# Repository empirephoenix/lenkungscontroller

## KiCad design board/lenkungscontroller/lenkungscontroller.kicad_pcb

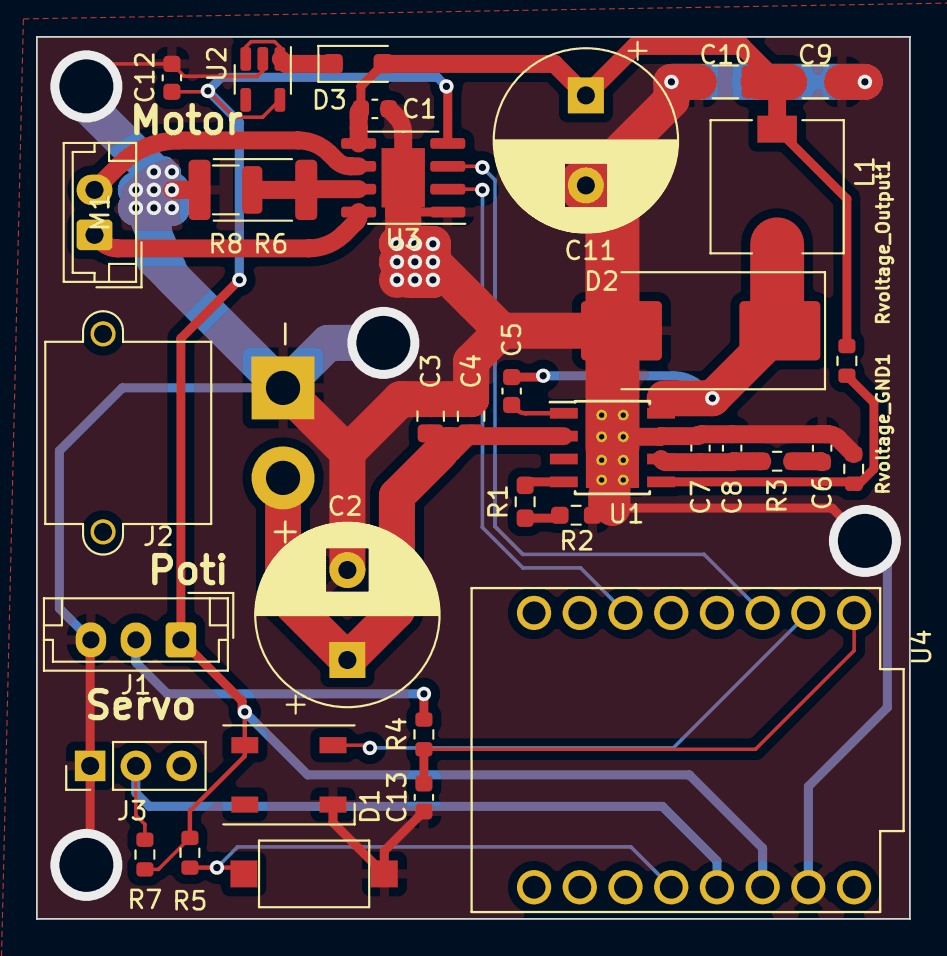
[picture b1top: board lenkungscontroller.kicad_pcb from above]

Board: 2 copper layers, 48.5 x 49.0 mm, 36 parts (0 on the bottom side), 22 nets.

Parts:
Boot1: Boot; SW_SPST_CK_RS282G05A3
C1: 220nF 50v x5r; C_0603_1608Metric
C2: 220uF; CP_Radial_D10.0mm_P5.00mm
C3, C4: 2.2uF 60V; C_0805_2012Metric
C5, C13: 100nF; C_0603_1608Metric
C6: 6800pF; C_0603_1608Metric
C7, C8: 39pf; C_0603_1608Metric
C9, C10: 47uF; C_1206_3216Metric
C11: 1000uF; CP_Radial_D10.0mm_P5.00mm
C12: 22uF; C_0603_1608Metric
D1: WS2812B; LED_WS2812B_PLCC4_5.0x5.0mm_P3.2mm
D2: SS56; D_SMC_Handsoldering
D3: D; D_SOD-123F
J1: Conn_01x03; JST_EH_B3B-EH-A_1x03_P2.50mm_Vertical
J2: Conn_01x02_Female; AMASS_XT30PW-M_1x02_P2.50mm_Horizontal
J3: Conn_01x03; PinHeader_1x03_P2.54mm_Vertical
L1: 8.2uH; L_7.3x7.3_H3.5
M1: Conn_01x02_Male; JST_EH_B2B-EH-A_1x02_P2.50mm_Vertical
R1, R2: 82k; R_0603_1608Metric_Pad0.98x0.95mm_HandSolder
R3: 13k; R_0603_1608Metric
R4, R5, R7: 1k; R_0603_1608Metric
R6: 1.5; R_2512_6332Metric
R8: 1.5; R_1210_3225Metric
Rvoltage_GND1: 1k; R_0603_1608Metric
Rvoltage_Output1: 14k; R_0603_1608Metric
U1: TPS54360DDA; TI_SO-PowerPAD-8_ThermalVias
U2: SPX3819M5-L-3-3; SOT-23-5
U3: A4950E; SOIC-8-1EP_3.9x4.9mm_P1.27mm_EP2.41x3.3mm
U4: ESP32-C3_SUPERMINI; MODULE_ESP32-C3_SUPERMINI

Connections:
3_3V: C12.1, D1.1 (VDD), J1.1, R5.1, R7.1, U2.5 (OUT), U3.4 (VREF), U4.3.3 (3V3)
12V: C1.2, C9.1, C10.1, C11.1, D3.2 (A), L1.2, Rvoltage_Output1.1, U3.5 (VBB)
Calibrate: Boot1.2, R5.2, U4.3 (GPIO3)
GND: Boot1.1, C1.1, C2.2, C3.2, C4.2, C6.2, C7.2, C8.2, C9.2, C10.2, C11.2, C12.2, C13.2, D1.3 (VSS), D2.2 (A), J1.3, J2.1, J3.1, R2.2, R6.2, R8.2, Rvoltage_GND1.2, U1.7 (GND), U1.9 (GNDPAD), U2.2 (GND), U3.1 (GND), U3.9 (PAD), U4.G (GND)
IN1: U3.3 (IN1), U4.7 (GPIO7)
IN2: U3.2 (IN2), U4.10 (GPIO10)
unnamed: C6.1, R3.2
unnamed: C5.2, D2.1 (K), L1.1, U1.8 (SW)
unnamed: D3.1 (K), U2.1 (IN), U2.3 (EN)
unnamed: J1.2, R4.2
unnamed: M1.1, U3.8 (OUT2)
unnamed: M1.2, U3.6 (OUT1)
unnamed: R1.2, R2.1
unnamed: C5.1, U1.1 (BOOT)
unnamed: C7.1, C8.1, R3.1, U1.6 (COMP)
unnamed: Rvoltage_GND1.1, Rvoltage_Output1.2, U1.5 (FB)
unnamed: R1.1, U1.4 (RT/CLK)
unnamed: R6.1, R8.1, U3.7 (LSS)
Poti: C13.1, R4.1, U4.5 (GPIO5)
Signal_In: J3.2, R7.2, U4.4 (GPIO4)
Status: D1.4 (DIN), U4.6 (GPIO6)
VIN: C2.1, C3.1, C4.1, J2.2, U1.2 (VIN)

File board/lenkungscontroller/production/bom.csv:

Designator,Footprint,Quantity,Value,LCSC Part #
Boot1,SW_SPST_CK_RS282G05A3,1,Boot,C72443
C1,0603,1,220nF 50v x5r,C64705
"C10, C9",1206,2,47uF,C96123
C11,CP_Radial_D10.0mm_P5.00mm,1,1000uF,C503217
C12,0603,1,22uF,C59461
"C13, C5",0603,2,100nF,C14663
C2,CP_Radial_D10.0mm_P5.00mm,1,220uF,C503217
"C3, C4",0805,2,2.2uF 60V,C49217
C6,0603,1,6800pF,C1631
"C7, C8",0603,2,39pf,C1666
D1,LED_WS2812B_PLCC4_5.0x5.0mm_P3.2mm,1,WS2812B,no
D2,D_SMC_Handsoldering,1,SS56,C4944963
D3,D_SOD-123F,1,D,
J1,JST_EH_B3B-EH-A_1x03_P2.50mm_Vertical,1,Conn_01x03,
J2,AMASS_XT30PW-M_1x02_P2.50mm_Horizontal,1,Conn_01x02_Female,C108769
J3,PinHeader_1x03_P2.54mm_Vertical,1,Conn_01x03,
L1,L_7.3x7.3_H3.5,1,8.2uH,C5189935
M1,JST_EH_B2B-EH-A_1x02_P2.50mm_Vertical,1,Conn_01x02_Male,
"R1, R2",0603,2,82k,C23254
R3,0603,1,13k,C22797
"R4, R5, R7, Rvoltage_GND1",0603,4,1k,
R6,2512,1,1.5,C5127851
R8,1210,1,1.5,C5127851
Rvoltage_Output1,0603,1,14k,C3016340
U1,TI_SO-PowerPAD-8_ThermalVias,1,TPS54360DDA,C44377
U2,SOT-23-5,1,SPX3819M5-L-3-3,C5370980
U3,SOIC-8-1EP_3.9x4.9mm_P1.27mm_EP2.41x3.3mm,1,A4950E,C82404
U4,MODULE_ESP32-C3_SUPERMINI,1,ESP32-C3_SUPERMINI,

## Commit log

2024-04-27 updated steering controller
